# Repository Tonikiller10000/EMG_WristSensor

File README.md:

# EMG WRIST SENSOR

## Description (Deprecated)
<b>This is an electromiography sensor witch can detect muscular activity.</b> 

After making the PCB, when working at the software, I found about it`s limitations.
With EMG(electromiography) you can detect the voltage produced by the muscle contraction, meaning that for you to recive a signal, you need to stay with the muscle contracted. 
For exemple, closing your hand into a relaxed fist will not generate signals, unless you clench it, and you will recive a electrical voltage(mV).
When you feel a touch the senzation goes trouth the nerves(deeper) rather than muscles with a weeker signal detectable only with needles.
The input is not verry precise at all, and is verry tiering to stay with the muscle contracted for a long time.

> [!WARNING]
> !!! do not use needles... it can cause infections, blood electrolisis, metal poisoning and other health risks.

<br>

<table>
  <tr>
    <td>
      
    </td>
    <td>
      
    </td>
  </tr>
</table>

<table>
  <tr>
    <td>
        <p align="center">
            
        </p>
    </td>
    <td>
        <p align="center">
            
        </p>
    </td>
  </tr>
</table>

<table>
  <tr>
    <td valign="top" width="50%">
        <h3>Detected actions:</h3>
        <ul style="list-style-type: none; padding-left: 20px;">
            <li> relaxed palm</li>
            <li> tigth fist</li>
            <li> extended palm</li>
            <li> wrist movements up/down</li>
            <li> snap</li>
            <li> press</li>
            <li> other...</li>
        </ul>
        <br>
    </td>
    <td valign="top" width="50%">
        <h3> OBSERVATIONS:</h3>
        <ul style="list-style-type: none; padding-left: 20px;">
            <li> missing 1.5K resistor to USB_DP </li>
            <li> wrong RGB footprint</li>
            <li> try using flex pcb</li>
            <li> add FMG</li>
        </ul>
    </td>
  </tr>
</table>

<br>

## How it works & user instructions
- it has 6 pairs of diferential op amps each with a variable gain potentiometer. (it removes the 50-60hz noice from the grid) (all differential op amps have a common offset potentiometer)
- each output goes trouth an op amp with another gain potentiometer, and then It goes to an STM ADC pin
- then data is scanned and sent to the usb virtual port and can be read with a plotter
- when using it, connect the gnd to the skin so it dosen`t stay floating and produce electrostatis shots.
- !!! when programming with a STLINK, power it via the usb and disconnect the power pin from stlink to stm (keep the gnd common reference)
- use an [Online serial plotter](https://web-serial-plotter.atomic14.com/) or [Serial Studio Pro](https://serial-studio.com/) to see the USB data.
- More papers on the subject at [BioSignals Detection Documents folder](https://github.com/Tonikiller10000/EMG_WristSensor/tree/main/BioSignalsDetectionDocuments)

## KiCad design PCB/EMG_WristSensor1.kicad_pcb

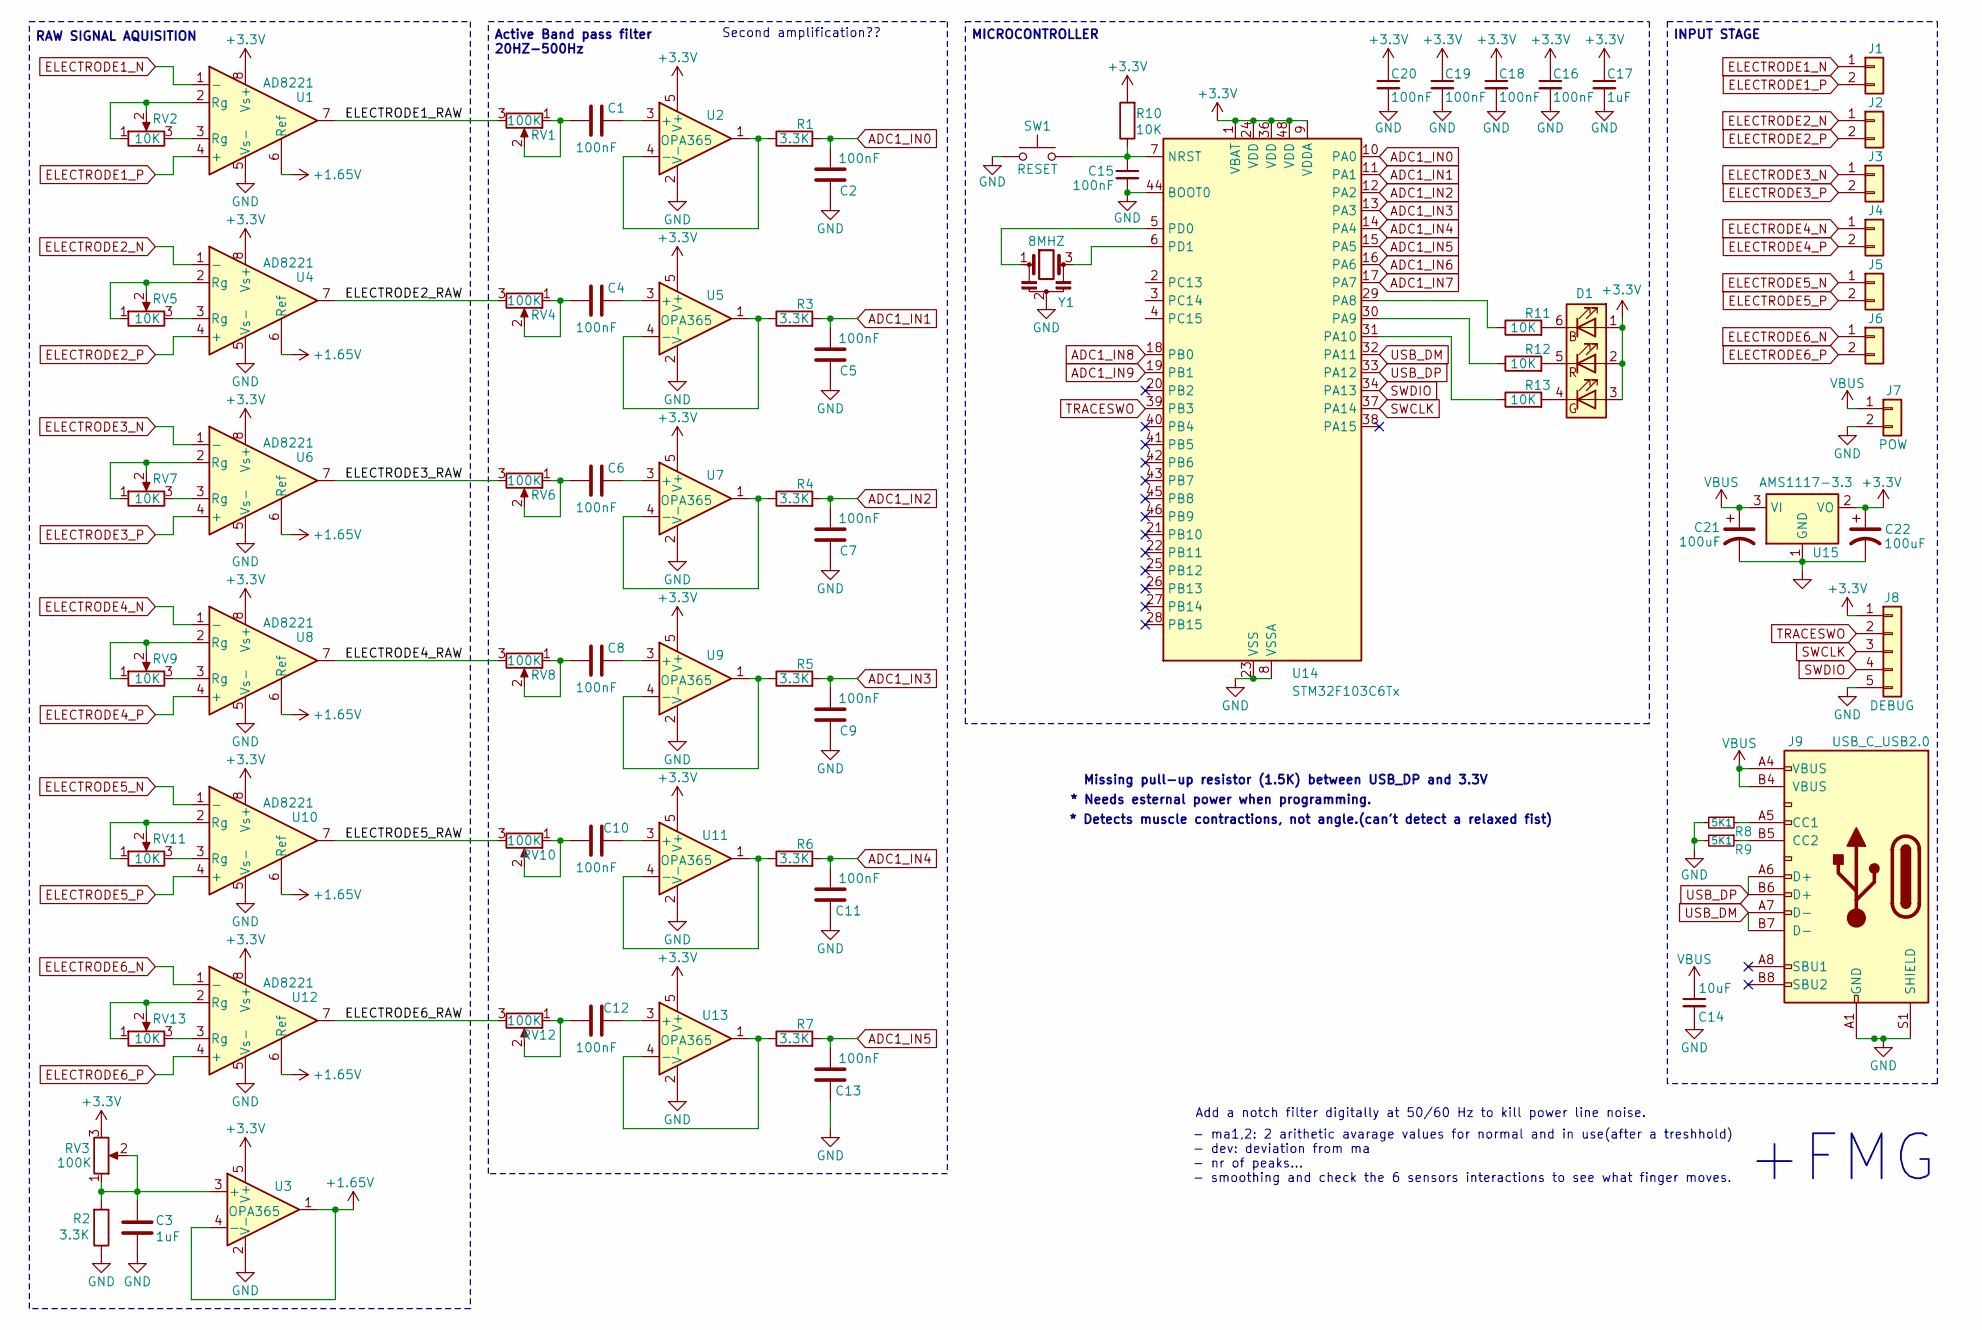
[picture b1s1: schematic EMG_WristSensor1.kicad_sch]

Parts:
C1, C2, C4, C5, C6, C7, C8, C9, C10, C11, C12, C13: 100nF; C_0603_1608Metric_Pad1.08x0.95mm_HandSolder
C3: 1uF; C_0603_1608Metric_Pad1.08x0.95mm_HandSolder
C14: 10uF
C15, C16, C18, C19, C20: 100nF; C_0402_1005Metric_Pad0.74x0.62mm_HandSolder
C17: 1uF; C_0402_1005Metric_Pad0.74x0.62mm_HandSolder
C21, C22: 100uF; C_1210_3225Metric_Pad1.33x2.70mm_HandSolder
D1: SMLVN6RGB; LED_ROHM_SMLVN6
J1, J2, J3, J4, J5, J6: Conn_01x02
J7: POW
J8: DEBUG
J9: USB_C_USB2.0
R1, R2, R3, R4, R5, R6, R7: 3.3K; R_0603_1608Metric_Pad0.98x0.95mm_HandSolder
R8, R9: 5K1; R_0402_1005Metric_Pad0.72x0.64mm_HandSolder
R10, R11, R12, R13: 10K; R_0603_1608Metric_Pad0.98x0.95mm_HandSolder
RV1, RV3, RV4, RV6, RV8, RV10, RV12: 100K; Potentiometer_Bourns_TC33X_Vertical
RV2, RV5, RV7, RV9, RV11, RV13: 10K; Potentiometer_Bourns_TC33X_Vertical
SW1: RESET
U1, U4, U6, U8, U10, U12: AD8221; SOP-8_3.9x4.9mm_P1.27mm
U2, U3, U5, U7, U9, U11, U13: OPA365; SOT-23-5
U14: STM32F103C6Tx; LQFP-48_7x7mm_P0.5mm
U15: AMS1117-3.3; SOT-223-3_TabPin2
Y1: 8MHZ

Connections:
+1.65V: U1.6 (Ref), U3.1, U3.4 (-), U4.6 (Ref), U6.6 (Ref), U8.6 (Ref), U10.6 (Ref), U12.6 (Ref)
+3.3V: C16.1, C17.1, C18.1, C19.1, C20.1, C22.1, D1.1 (BA), D1.2 (RA), D1.3 (GA), J8.1, R10.2, RV3.3, U1.8 (Vs+), U2.5 (V+), U3.5 (V+), U4.8 (Vs+), U5.5 (V+), U6.8 (Vs+), U7.5 (V+), U8.8 (Vs+), U9.5 (V+), U10.8 (Vs+), U11.5 (V+), U12.8 (Vs+), U13.5 (V+), U14.1 (VBAT), U14.9 (VDDA), U14.24 (VDD), U14.36 (VDD), U14.48 (VDD), U15.2 (VO)
/ELECTRODE1_RAW: RV1.3, U1.7
/ELECTRODE2_RAW: RV4.3, U4.7
/ELECTRODE3_RAW: RV6.3, U6.7
/ELECTRODE4_RAW: RV8.3, U8.7
/ELECTRODE5_RAW: RV10.3, U10.7
/ELECTRODE6_RAW: RV12.3, U12.7
ADC1_IN0: C2.1, R1.2, U14.10 (PA0)
ADC1_IN1: C5.1, R3.2, U14.11 (PA1)
ADC1_IN2: C7.1, R4.2, U14.12 (PA2)
ADC1_IN3: C9.1, R5.2, U14.13 (PA3)
ADC1_IN4: C11.1, R6.2, U14.14 (PA4)
ADC1_IN5: C13.1, R7.2, U14.15 (PA5)
ADC1_IN6: U14.16 (PA6)
ADC1_IN7: U14.17 (PA7)
ADC1_IN8: U14.18 (PB0)
ADC1_IN9: U14.19 (PB1)
ELECTRODE1_N: J1.1, U1.1 (-)
ELECTRODE1_P: J1.2, U1.4 (+)
ELECTRODE2_N: J2.1, U4.1 (-)
ELECTRODE2_P: J2.2, U4.4 (+)
ELECTRODE3_N: J3.1, U6.1 (-)
ELECTRODE3_P: J3.2, U6.4 (+)
ELECTRODE4_N: J4.1, U8.1 (-)
ELECTRODE4_P: J4.2, U8.4 (+)
ELECTRODE5_N: J5.1, U10.1 (-)
ELECTRODE5_P: J5.2, U10.4 (+)
ELECTRODE6_N: J6.1, U12.1 (-)
ELECTRODE6_P: J6.2, U12.4 (+)
GND: C2.2, C3.2, C5.2, C7.2, C9.2, C11.2, C13.2, C14.2, C15.2, C16.2, C17.2, C18.2, C19.2, C20.2, C21.2, C22.2, J7.2, J8.5, J9.A1 (GND), J9.B1 (GND), J9.S1 (SHIELD), R2.1, R8.2, R9.2, SW1.1, U1.5 (Vs-), U2.2 (V-), U3.2 (V-), U4.5 (Vs-), U5.2 (V-), U6.5 (Vs-), U7.2 (V-), U8.5 (Vs-), U9.2 (V-), U10.5 (Vs-), U11.2 (V-), U12.5 (Vs-), U13.2 (V-), U14.8 (VSSA), U14.23 (VSS), U14.35 (VSS), U14.44 (BOOT0), U14.47 (VSS), U15.1 (GND), Y1.2
unnamed: C1.1, RV1.1, RV1.2
unnamed: C4.1, RV4.1, RV4.2
unnamed: C6.1, RV6.1, RV6.2
unnamed: C8.1, RV8.1, RV8.2
unnamed: C10.1, RV10.1, RV10.2
unnamed: C12.1, RV12.1, RV12.2
unnamed: D1.6 (BK), R11.2
unnamed: D1.4 (GK), R13.2
unnamed: D1.5 (RK), R12.2
unnamed: J9.A5 (CC1), R8.1
unnamed: J9.B5 (CC2), R9.1
unnamed: RV2.1, RV2.2, U1.2 (Rg)
unnamed: RV2.3, U1.3 (Rg)
unnamed: RV5.1, RV5.2, U4.2 (Rg)
unnamed: RV5.3, U4.3 (Rg)
unnamed: RV7.1, RV7.2, U6.2 (Rg)
unnamed: RV7.3, U6.3 (Rg)
unnamed: RV9.1, RV9.2, U8.2 (Rg)
unnamed: RV9.3, U8.3 (Rg)
unnamed: RV11.1, RV11.2, U10.2 (Rg)
unnamed: RV11.3, U10.3 (Rg)
unnamed: RV13.1, RV13.2, U12.2 (Rg)
unnamed: RV13.3, U12.3 (Rg)
unnamed: C1.2, U2.3 (+)
unnamed: R1.1, U2.1, U2.4 (-)
unnamed: C3.1, R2.2, RV3.1, RV3.2, U3.3 (+)
unnamed: C4.2, U5.3 (+)
unnamed: R3.1, U5.1, U5.4 (-)
unnamed: C6.2, U7.3 (+)
unnamed: R4.1, U7.1, U7.4 (-)
unnamed: C8.2, U9.3 (+)
unnamed: R5.1, U9.1, U9.4 (-)
unnamed: C10.2, U11.3 (+)
unnamed: R6.1, U11.1, U11.4 (-)
unnamed: C12.2, U13.3 (+)
unnamed: R7.1, U13.1, U13.4 (-)
unnamed: C15.1, R10.1, SW1.2, U14.7 (NRST)
unnamed: R11.1, U14.29 (PA8)
unnamed: R12.1, U14.30 (PA9)
unnamed: R13.1, U14.31 (PA10)
unnamed: U14.5 (PD0), Y1.1
unnamed: U14.6 (PD1), Y1.3
SWCLK: J8.3, U14.37 (PA14)
SWDIO: J8.4, U14.34 (PA13)
TRACESWO: J8.2, U14.39 (PB3)
USB_DM: J9.A7 (D-), J9.B7 (D-), U14.32 (PA11)
USB_DP: J9.A6 (D+), J9.B6 (D+), U14.33 (PA12)
VBUS: C14.1, C21.1, J7.1, J9.A4 (VBUS), J9.B4 (VBUS), U15.3 (VI)

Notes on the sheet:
* Detects muscle contractions, not angle.(can't detect a relaxed fist)
- ma1,2: 2 arithetic avarage values for normal and in use(after a treshhold) - dev: deviation from ma - nr of peaks... - smoothing and check the 6 sensors interactions to see what finger moves.
Add a notch filter digitally at 50/60 Hz to kill power line noise.
+FMG
Second amplification??
MICROCONTROLLER
RAW SIGNAL AQUISITION
Missing pull-up resistor (1.5K) between USB_DP and 3.3V
Active Band pass filter 20HZ-500Hz
INPUT STAGE
* Needs esternal power when programming.

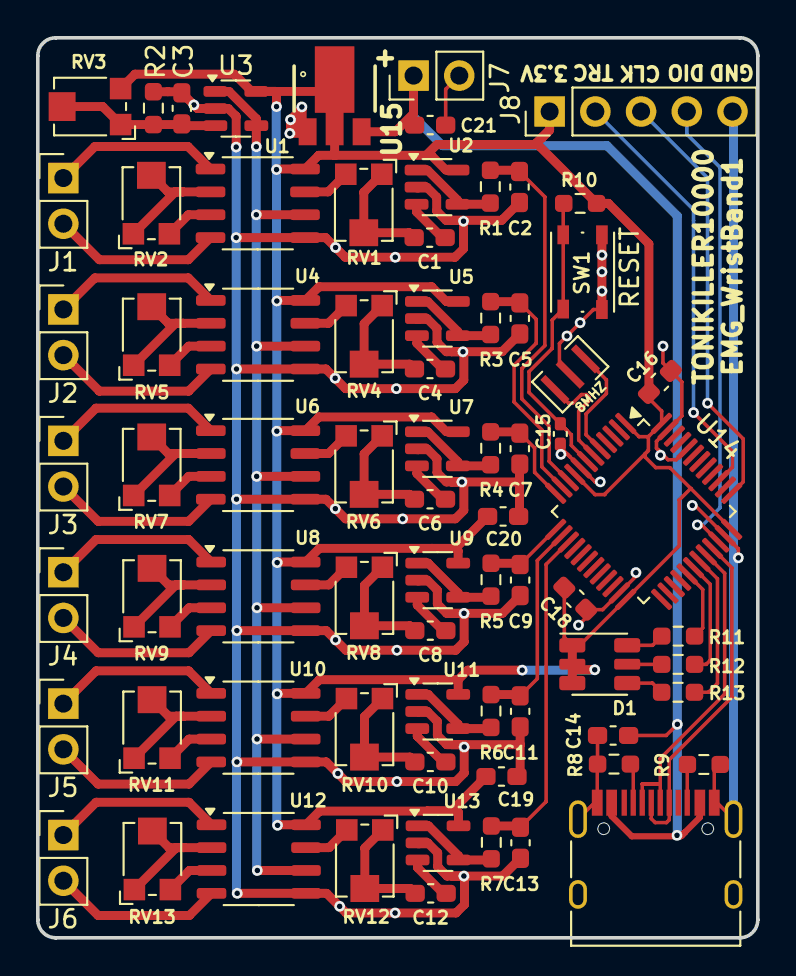
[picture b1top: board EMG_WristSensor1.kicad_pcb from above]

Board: 2 copper layers, 40.0 x 50.0 mm, 73 parts (0 on the bottom side), 75 nets.

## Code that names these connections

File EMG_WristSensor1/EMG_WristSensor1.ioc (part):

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Mcu.Name=STM32F103C(4-6)Tx
Mcu.Package=LQFP48
Mcu.UserName=STM32F103C6Tx
PA0-WKUP.Signal=ADCx_IN0
PA1.Signal=ADCx_IN1
PA11.Mode=Device
PA11.Signal=USB_DM
PA12.Mode=Device
PA12.Signal=USB_DP
PA13.Mode=Trace_Asynchronous_SW
PA13.Signal=SYS_JTMS-SWDIO
PA14.Mode=Trace_Asynchronous_SW
PA14.Signal=SYS_JTCK-SWCLK
PA2.Signal=ADCx_IN2
PA3.Signal=ADCx_IN3
PA4.Signal=ADCx_IN4
PA5.Signal=ADCx_IN5
PA6.Signal=ADCx_IN6
PA7.Signal=ADCx_IN7
PB0.Signal=ADCx_IN8
PB1.Signal=ADCx_IN9
PB3.Mode=Trace_Asynchronous_SW
PB3.Signal=SYS_JTDO-TRACESWO
PD0-OSC_IN.Mode=HSE-External-Oscillator
PD0-OSC_IN.Signal=RCC_OSC_IN
PD1-OSC_OUT.Mode=HSE-External-Oscillator
PD1-OSC_OUT.Signal=RCC_OSC_OUT
RCC.SYSCLKFreq_VALUE=72000000
RCC.SYSCLKSource=RCC_SYSCLKSOURCE_PLLCLK
board=custom

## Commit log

2026-05-20 init
